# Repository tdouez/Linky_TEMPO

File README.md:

//--------------------------------------------------------------------
//   __|              _/           _ )  |
//   _| |  |   ` \    -_)   -_)    _ \  |   -_)  |  |   -_)
//  _| \_,_| _|_|_| \___| \___|   ___/ _| \___| \_,_| \___|
//--------------------------------------------------------------------
# Linky_TEMPO

Module de récupération des sorties relais pour le compteur Linky avec un contrat TEMPO
Compatible en TIC historique et standard

- Description disponible sur http://fumeebleue.fr

------------------------------------------------------------------------------------
Code mise à disposition selon les termes de la Licence Creative Commons Attribution
Pas d’Utilisation Commerciale.
Partage dans les Mêmes Conditions 4.0 International.
------------------------------------------------------------------------------------

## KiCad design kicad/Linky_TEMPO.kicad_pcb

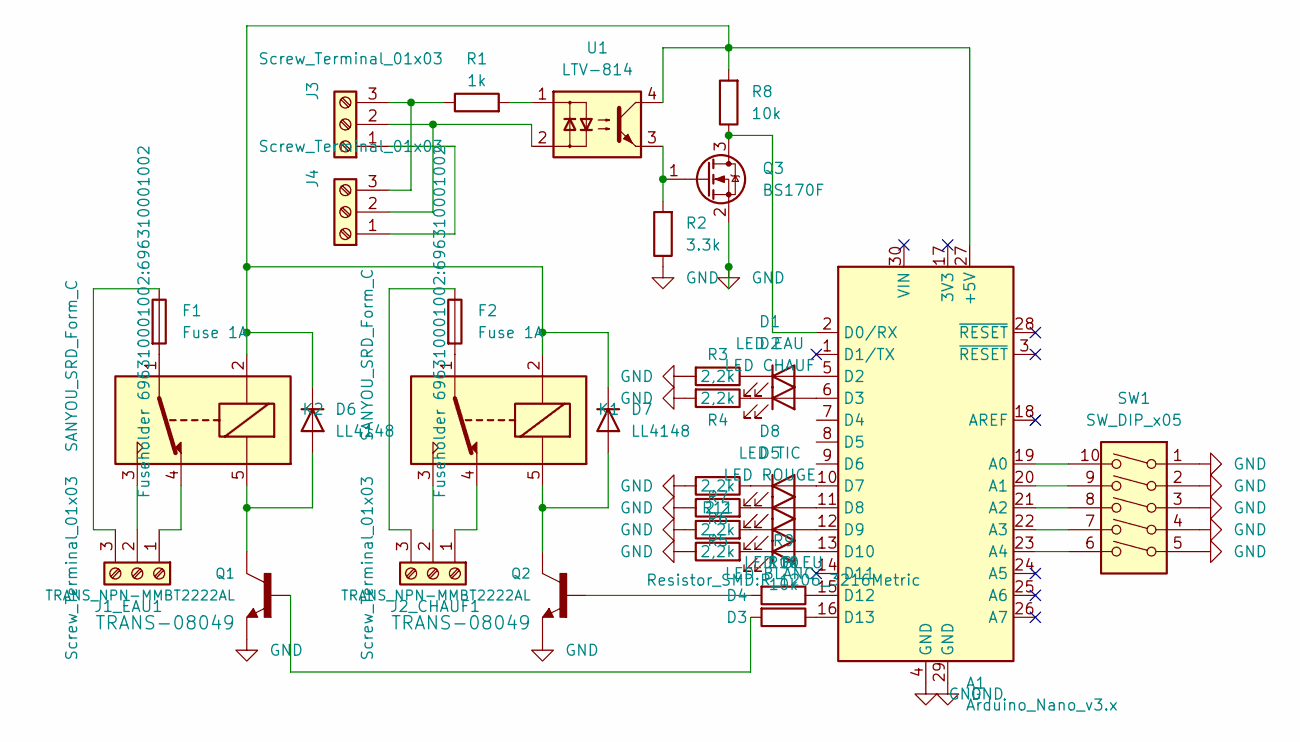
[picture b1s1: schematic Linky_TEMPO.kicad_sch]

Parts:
A1: Arduino_Nano_v3.x; Arduino_Nano
D1: LED EAU; LED_D3.0mm_FlatTop
D2: LED CHAUF; LED_D3.0mm_FlatTop
D3: LED BLEU; LED_D3.0mm_FlatTop
D4: LED BLANC; LED_D3.0mm_FlatTop
D5: LED ROUGE; LED_D3.0mm_FlatTop
D6, D7: LL4148; D_MiniMELF
D8: LED TIC; LED_D3.0mm_FlatTop
F1, F2: Fuse 1A; 696310001002
J1_EAU1, J2_CHAUF1, J3, J4: Screw_Terminal_01x03; TerminalBlock_Altech_AK300-3_P5.00mm
K1, K2: SANYOU_SRD_Form_C; Relay_SPDT_SANYOU_SRD_Series_Form_C
Q1, Q2: TRANS_NPN-MMBT2222AL; SOT-23
Q3: BS170F; SOT-23
R1: 1k; R_1206_3216Metric
R2: 3.3k; R_1206_3216Metric
R3, R4, R5, R6, R11: 2,2k; R_1206_3216Metric
R7: 2,2; R_1206_3216Metric
R8, R9, R10: 10k; R_1206_3216Metric
SW1: SW_DIP_x05; SW_DIP_SPSTx05_Slide_9.78x14.88mm_W7.62mm_P2.54mm
U1: LTV-814; DIP-4_W7.62mm

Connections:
GND: A1.4 (GND), A1.29 (GND), Q1.2 (E), Q2.2 (E), Q3.2 (S), R2.1, R3.2, R4.2, R5.1, R6.1, R7.1, R11.2, SW1.1, SW1.2, SW1.3, SW1.4, SW1.5
unnamed: A1.27 (+5V), D6.1 (K), D7.1 (K), K1.2, K2.2, R8.2, U1.4
unnamed: A1.19 (A0), SW1.10
unnamed: A1.20 (A1), SW1.9
unnamed: A1.21 (A2), SW1.8
unnamed: A1.22 (A3), SW1.7
unnamed: A1.23 (A4), SW1.6
unnamed: A1.2 (D0/RX), Q3.3 (D), R8.1
unnamed: A1.5 (D2), D1.2 (A)
unnamed: A1.6 (D3), D2.2 (A)
unnamed: A1.10 (D7), D8.2 (A)
unnamed: A1.11 (D8), D5.2 (A)
unnamed: A1.12 (D9), D4.2 (A)
unnamed: A1.13 (D10), D3.2 (A)
unnamed: A1.15 (D12), R9.1
unnamed: A1.16 (D13), R10.1
unnamed: D1.1 (K), R3.1
unnamed: D2.1 (K), R4.1
unnamed: D3.1 (K), R5.2
unnamed: D4.1 (K), R6.2
unnamed: D5.1 (K), R7.2
unnamed: D6.2 (A), K2.5, Q1.3 (C)
unnamed: D7.2 (A), K1.5, Q2.3 (C)
unnamed: D8.1 (K), R11.1
unnamed: F1.2, K2.1
unnamed: F2.2, K1.1
unnamed: J1_EAU1.1, K2.4
unnamed: J1_EAU1.2, K2.3
unnamed: F1.1, J1_EAU1.3
unnamed: J2_CHAUF1.1, K1.4
unnamed: J2_CHAUF1.2, K1.3
unnamed: F2.1, J2_CHAUF1.3
unnamed: J3.1, J4.1
unnamed: J3.2, J4.2, U1.2
unnamed: J3.3, J4.3, R1.1
unnamed: Q1.1 (B), R10.2
unnamed: Q2.1 (B), R9.2
unnamed: Q3.1 (G), R2.2, U1.3
unnamed: R1.2, U1.1

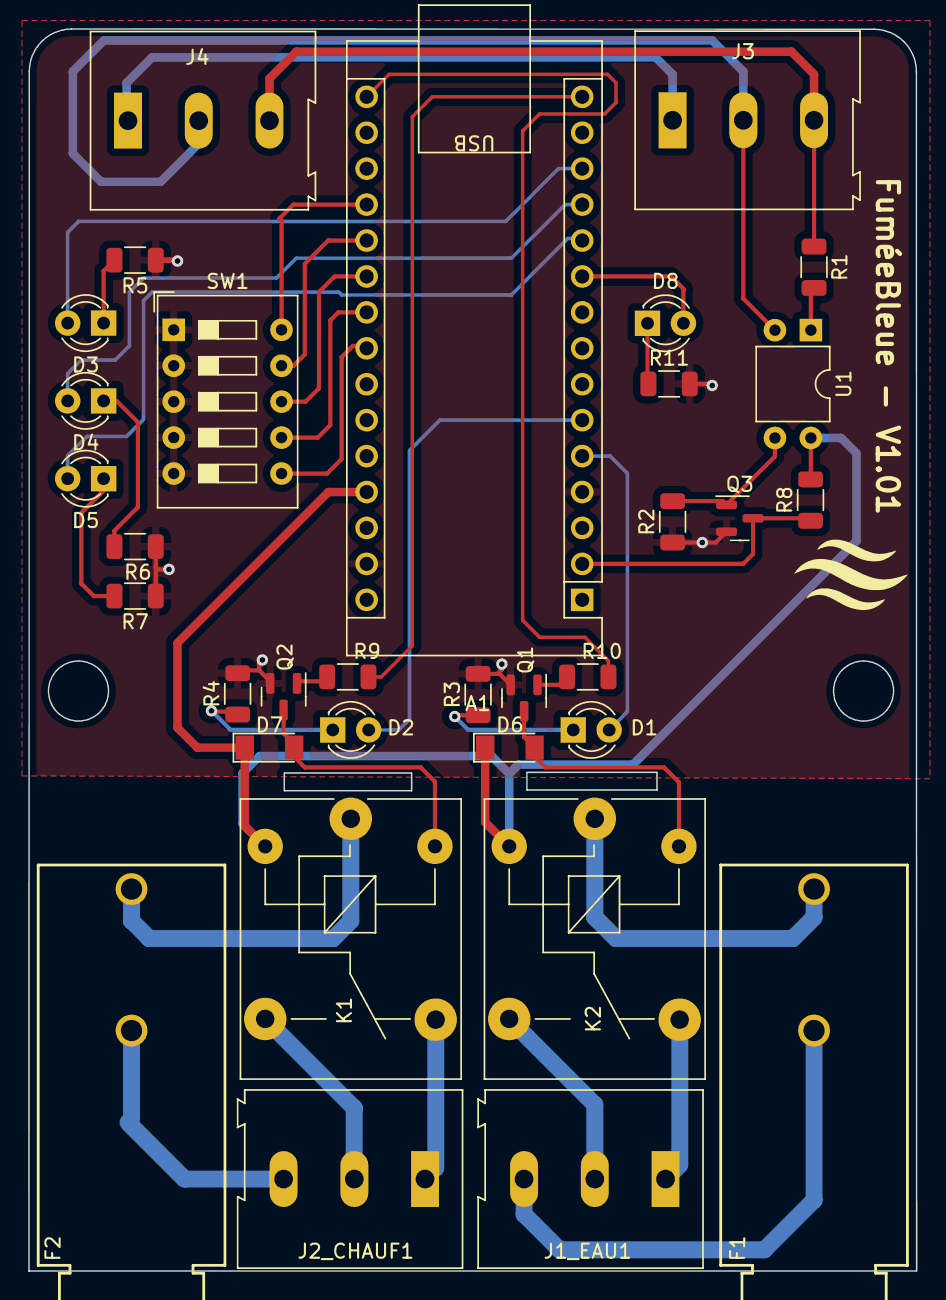
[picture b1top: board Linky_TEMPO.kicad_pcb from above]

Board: 2 copper layers, 62.7 x 87.8 mm, 33 parts (0 on the bottom side), 39 nets.

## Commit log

2023-02-09 Update pcb Kicad 1.0.1
    Update pcb Kicad 1.0.1
2023-02-17 v1.0.1 PCB
    v1.0.1 PCB Kicad
2023-02-17 V1.0.0
    Version initiale du logiciel pour l'arduino Nano
2023-03-04 v1.0.1
    Ajout sequence test led, correction détection TEMPO histo & standard, utilisation libTeleinfoLite
2023-03-08 Create LICENSE
2023-03-13 v1.0.2
    Correction sur programmation CHAUF/EAU
2023-03-19 v1.0.3
    Correction sur lecture switch
2023-03-24 v1.0.4
    Correction sur inversion sorties relais eau/chauf.
2023-04-27 v1.0.5
    Correction sur la detection du mode TIC standard
2023-06-18 v1.1.0
    Ajout visualisation couleur lendemain
2023-07-12 v1.2.0
    Inversion ordre relais, les relais seront moins sollicités. Modif affichage detection des modes TIC, clignotement des leds rouges ou led bleu en plus de la led verte.
2023-07-13 PCB v1.01
2023-07-22 v1.2.1
    Ajout traces debug. Inversion relais eau.
2023-07-23 v1.2.2
    Correction détection passage HP/HC.
2023-08-02 v1.2.3
2023-11-04 v1.2.4
    Correction affichage couleur lendemain
2023-12-01 v1.2.5
    Correction détection couleur jour lendemain pour TIC standard.
2023-12-22 v1.3.0
